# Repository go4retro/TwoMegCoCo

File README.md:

# TwoMegCoCo - an SRAM-based 2048kB RAM Expansion for the TANDY Color Computer 3
A TTL logic, SRAM-based 2048kB (2MB) memory expansion for the Color Computer 3.  Upper bank registers are write-only, like the older Disto units. All parts are through hole for easy hobbyist assembly.

## Motivation

After acquiring a used Disto 2MB memory expansion, I wondered if a similar 1980's TTL-based solution could have been created using SRAM (ignoring the fact that 2MB of SRAM was extremely expensive at the time compared to DRAM), and I wanted to see if I could design a unit using only off-the-shelf TTL circuitry. (And, since, at time of writing this, the MMU extension PCB is still being debugged, the question is yet unanswered :-)).

Obviously, as with the HalfMegCoco project, there is little economic incentive in this project, as the contemporary commercial solutions offer more functionality at a cheaper price.  But, there's always some value in building a unit oneself, or at least understanding how the MMU process works by inspecting the actual TTL logic.

## Status

Currently, the SRAM board has been confirmed to work with various MMU extension solutions (Boysontech/Cloud9), but I am still designing and debugging the MMU board (would appreciate help, if there is interest).

## License
Copyright (C) 2020  RETRO Innovations

These files are free designs; you can redistribute them and/or modify
them under the terms of the Creative Commons Attribution-ShareAlike 
4.0 International License.

You should have received a copy of the license along with this
work. If not, see <http://creativecommons.org/licenses/by-sa/4.0/>.

These files are distributed in the hope that they will be useful,
but WITHOUT ANY WARRANTY; without even the implied warranty of
MERCHANTABILITY or FITNESS FOR A PARTICULAR PURPOSE.  See the
license for more details.

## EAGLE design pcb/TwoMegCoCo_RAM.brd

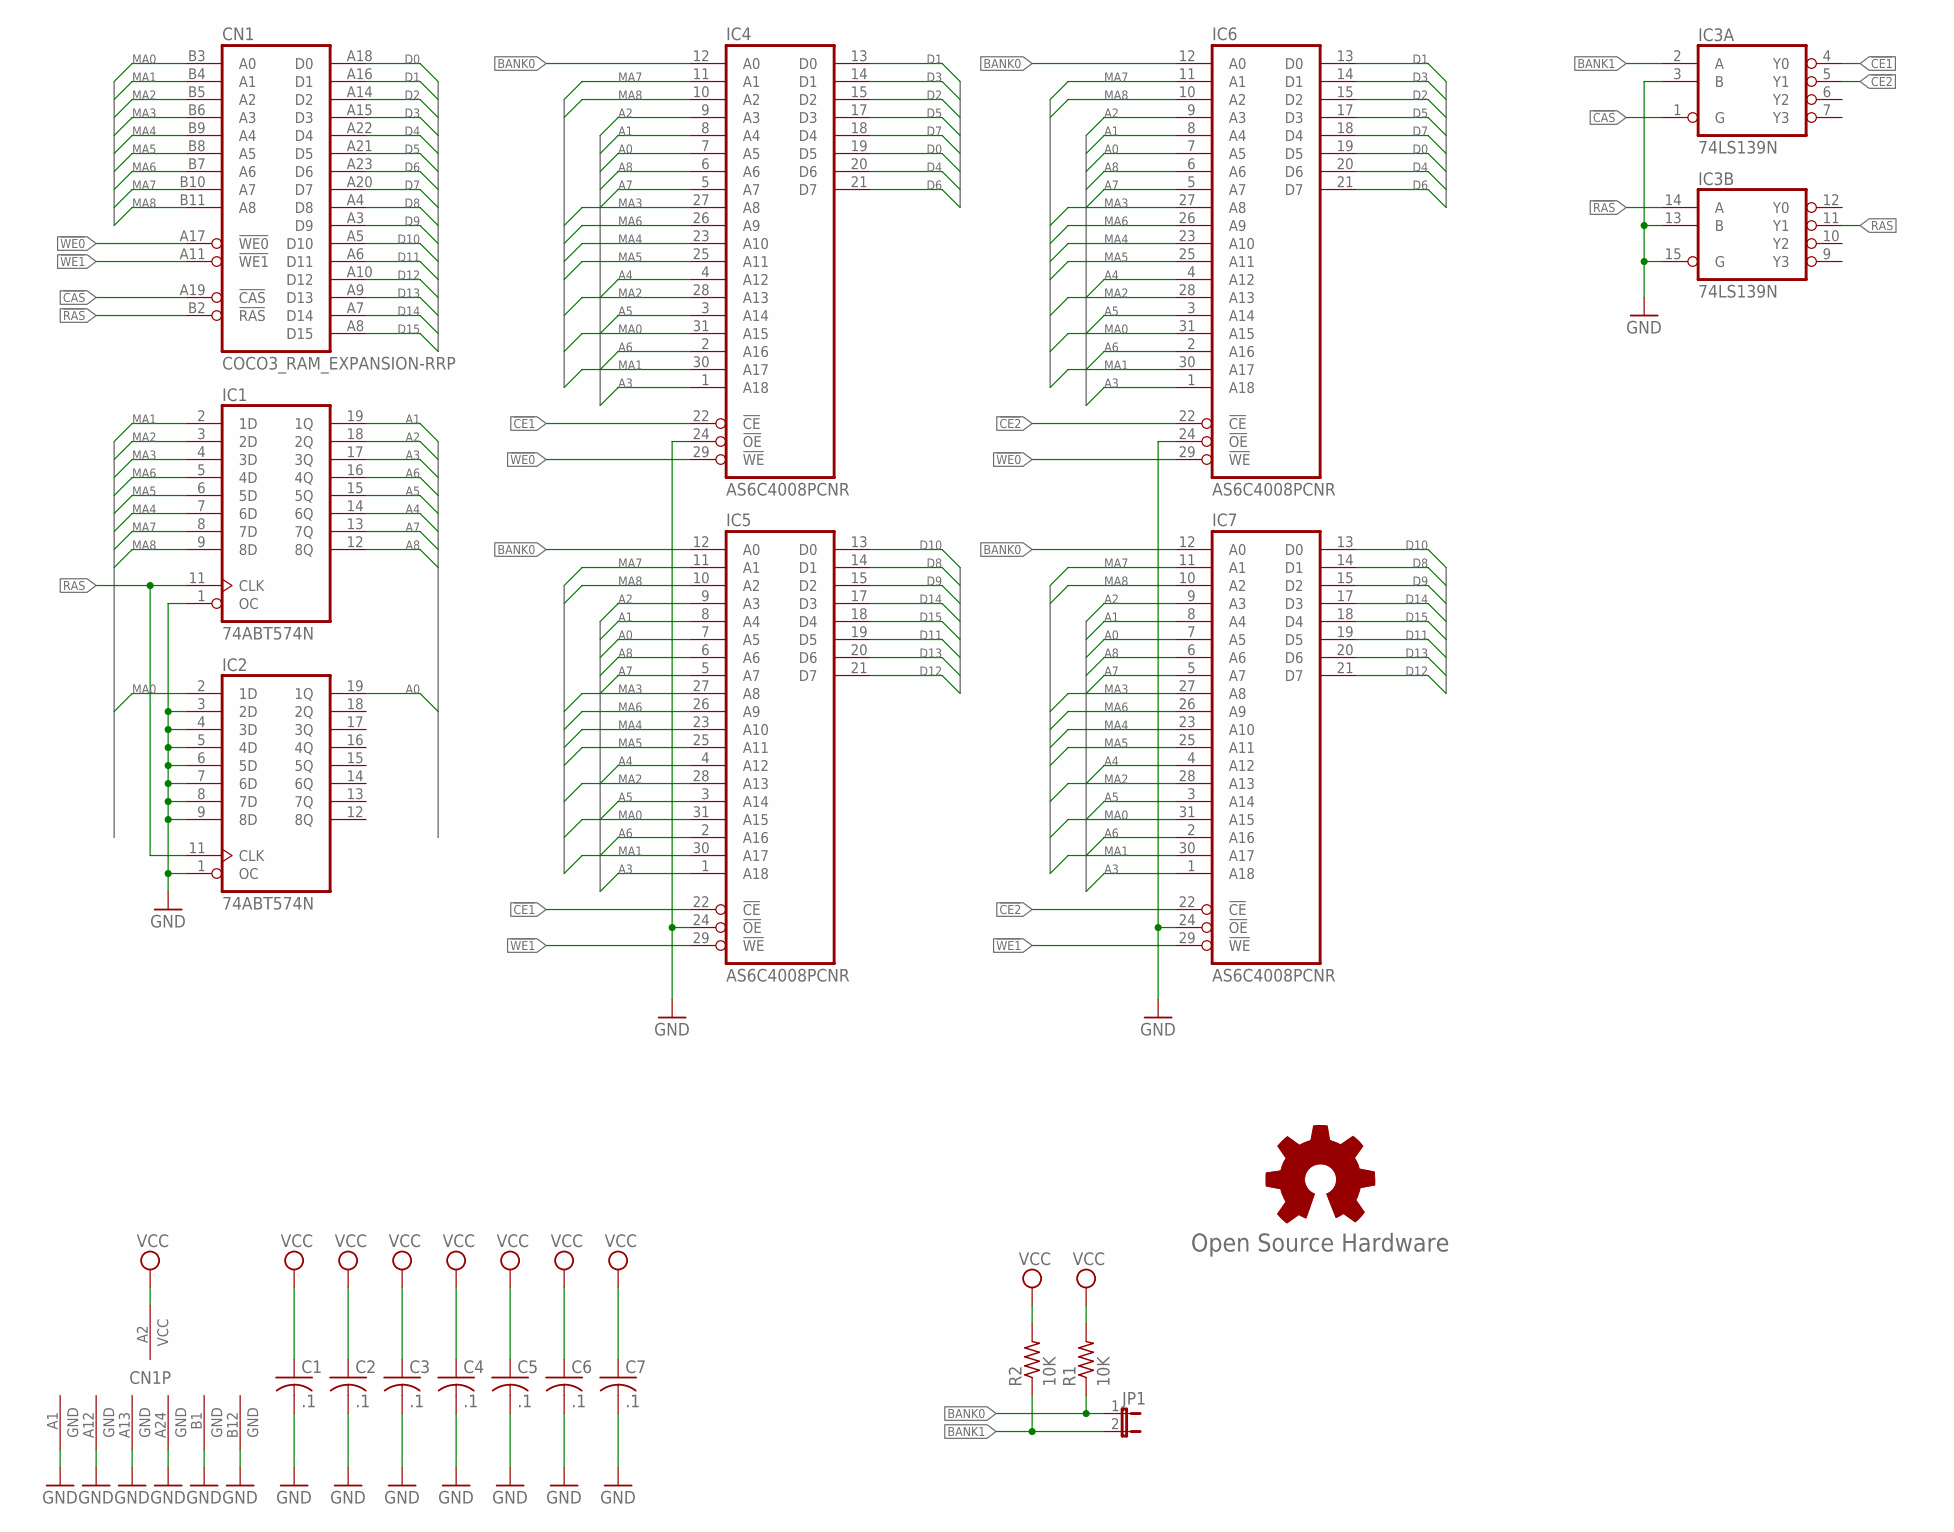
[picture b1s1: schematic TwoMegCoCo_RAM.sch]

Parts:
C1, C2, C3, C4, C5, C6, C7: .1; C025-025X050
CN1: COCO3_RAM_EXPANSION-RRP; RAM_EXPANSION_REV_RP
GOLD_ORB_SM1: Open Source Hardware; OSHW_8MM
IC1, IC2: 74ABT574N; DIL20-RP
IC3: 74LS139N; DIL16-RP
IC4, IC5, IC6, IC7: AS6C4008PCNR; DIL32-RP
JP1: JP1E; JP1
R1, R2: 10K; 0204/7

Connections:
!CAS: CN1.A19 (!CAS), IC3.1 (G)
!CE1: IC3.4 (Y0), IC4.22 (!CE), IC5.22 (!CE)
!CE2: IC3.5 (Y1), IC6.22 (!CE), IC7.22 (!CE)
!RAS: CN1.B2 (!RAS), IC3.14 (A)
!WE0: CN1.A17 (!WE0), IC4.29 (!WE), IC6.29 (!WE)
!WE1: CN1.A11 (!WE1), IC5.29 (!WE), IC7.29 (!WE)
A0: IC2.19 (1Q), IC4.7 (A5), IC5.7 (A5), IC6.7 (A5), IC7.7 (A5)
A1: IC1.19 (1Q), IC4.8 (A4), IC5.8 (A4), IC6.8 (A4), IC7.8 (A4)
A2: IC1.18 (2Q), IC4.9 (A3), IC5.9 (A3), IC6.9 (A3), IC7.9 (A3)
A3: IC1.17 (3Q), IC4.1 (A18), IC5.1 (A18), IC6.1 (A18), IC7.1 (A18)
A4: IC1.14 (6Q), IC4.4 (A12), IC5.4 (A12), IC6.4 (A12), IC7.4 (A12)
A5: IC1.15 (5Q), IC4.3 (A14), IC5.3 (A14), IC6.3 (A14), IC7.3 (A14)
A6: IC1.16 (4Q), IC4.2 (A16), IC5.2 (A16), IC6.2 (A16), IC7.2 (A16)
A7: IC1.13 (7Q), IC4.5 (A7), IC5.5 (A7), IC6.5 (A7), IC7.5 (A7)
A8: IC1.12 (8Q), IC4.6 (A6), IC5.6 (A6), IC6.6 (A6), IC7.6 (A6)
BANK0: IC4.12 (A0), IC5.12 (A0), IC6.12 (A0), IC7.12 (A0), JP1.1, R1.1
BANK1: IC3.2 (A), JP1.2, R2.1
D0: CN1.A18 (D0), IC4.19 (D5), IC6.19 (D5)
D1: CN1.A16 (D1), IC4.13 (D0), IC6.13 (D0)
D2: CN1.A14 (D2), IC4.15 (D2), IC6.15 (D2)
D3: CN1.A15 (D3), IC4.14 (D1), IC6.14 (D1)
D4: CN1.A22 (D4), IC4.20 (D6), IC6.20 (D6)
D5: CN1.A21 (D5), IC4.17 (D3), IC6.17 (D3)
D6: CN1.A23 (D6), IC4.21 (D7), IC6.21 (D7)
D7: CN1.A20 (D7), IC4.18 (D4), IC6.18 (D4)
D8: CN1.A4 (D8), IC5.14 (D1), IC7.14 (D1)
D9: CN1.A3 (D9), IC5.15 (D2), IC7.15 (D2)
D10: CN1.A5 (D10), IC5.13 (D0), IC7.13 (D0)
D11: CN1.A6 (D11), IC5.19 (D5), IC7.19 (D5)
D12: CN1.A10 (D12), IC5.21 (D7), IC7.21 (D7)
D13: CN1.A9 (D13), IC5.20 (D6), IC7.20 (D6)
D14: CN1.A7 (D14), IC5.17 (D3), IC7.17 (D3)
D15: CN1.A8 (D15), IC5.18 (D4), IC7.18 (D4)
GND: C1.2, C2.2, C3.2, C4.2, C5.2, C6.2, C7.2, CN1.A1 (GND), CN1.A12 (GND), CN1.A13 (GND), CN1.A24 (GND), CN1.B1 (GND), CN1.B12 (GND), IC1.1 (OC), IC1.10 (GND), IC2.1 (OC), IC2.3 (2D), IC2.4 (3D), IC2.5 (4D), IC2.6 (5D), IC2.7 (6D), IC2.8 (7D), IC2.9 (8D), IC2.10 (GND), IC3.3 (B), IC3.8 (GND), IC3.13 (B), IC3.15 (G), IC4.16 (GND), IC4.24 (!OE), IC5.16 (GND), IC5.24 (!OE), IC6.16 (GND), IC6.24 (!OE), IC7.16 (GND), IC7.24 (!OE)
MA0: CN1.B3 (A0), IC2.2 (1D), IC4.31 (A15), IC5.31 (A15), IC6.31 (A15), IC7.31 (A15)
MA1: CN1.B4 (A1), IC1.2 (1D), IC4.30 (A17), IC5.30 (A17), IC6.30 (A17), IC7.30 (A17)
MA2: CN1.B5 (A2), IC1.3 (2D), IC4.28 (A13), IC5.28 (A13), IC6.28 (A13), IC7.28 (A13)
MA3: CN1.B6 (A3), IC1.4 (3D), IC4.27 (A8), IC5.27 (A8), IC6.27 (A8), IC7.27 (A8)
MA4: CN1.B9 (A4), IC1.7 (6D), IC4.23 (A10), IC5.23 (A10), IC6.23 (A10), IC7.23 (A10)
MA5: CN1.B8 (A5), IC1.6 (5D), IC4.25 (A11), IC5.25 (A11), IC6.25 (A11), IC7.25 (A11)
MA6: CN1.B7 (A6), IC1.5 (4D), IC4.26 (A9), IC5.26 (A9), IC6.26 (A9), IC7.26 (A9)
MA7: CN1.B10 (A7), IC1.8 (7D), IC4.11 (A1), IC5.11 (A1), IC6.11 (A1), IC7.11 (A1)
MA8: CN1.B11 (A8), IC1.9 (8D), IC4.10 (A2), IC5.10 (A2), IC6.10 (A2), IC7.10 (A2)
RAS: IC1.11 (CLK), IC2.11 (CLK), IC3.11 (Y1)
VCC: C1.1, C2.1, C3.1, C4.1, C5.1, C6.1, C7.1, CN1.A2 (VCC), IC1.20 (VCC), IC2.20 (VCC), IC3.16 (VCC), IC4.32 (VCC), IC5.32 (VCC), IC6.32 (VCC), IC7.32 (VCC), R1.2, R2.2

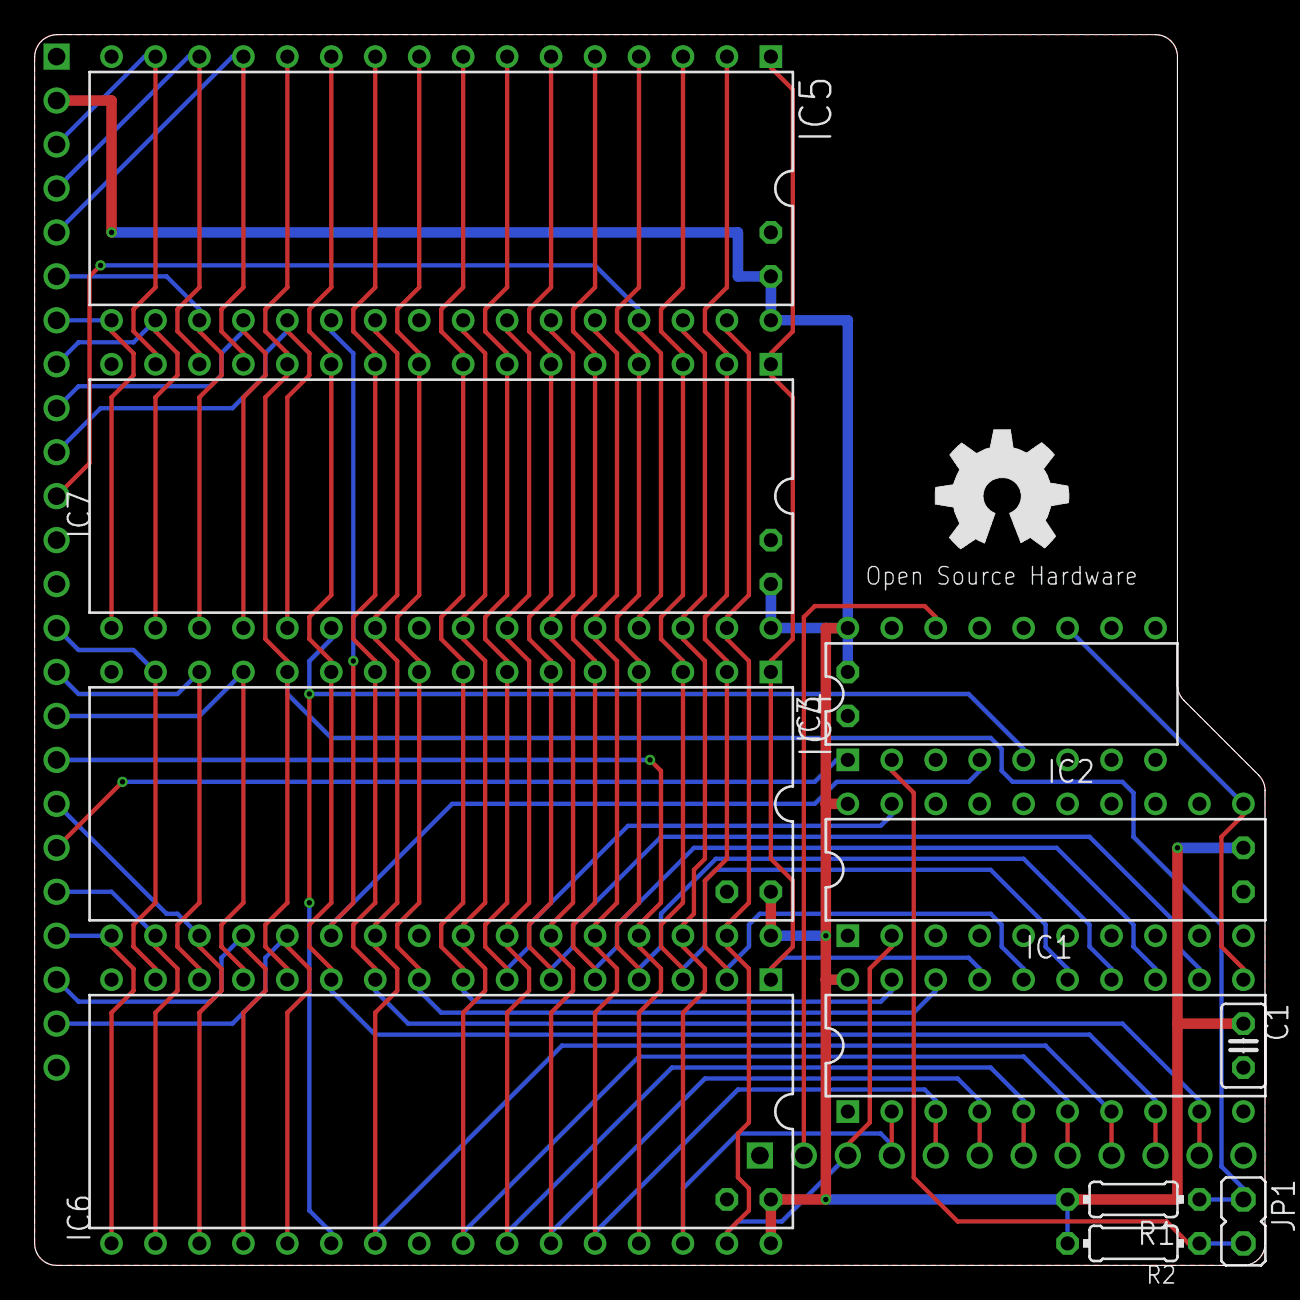
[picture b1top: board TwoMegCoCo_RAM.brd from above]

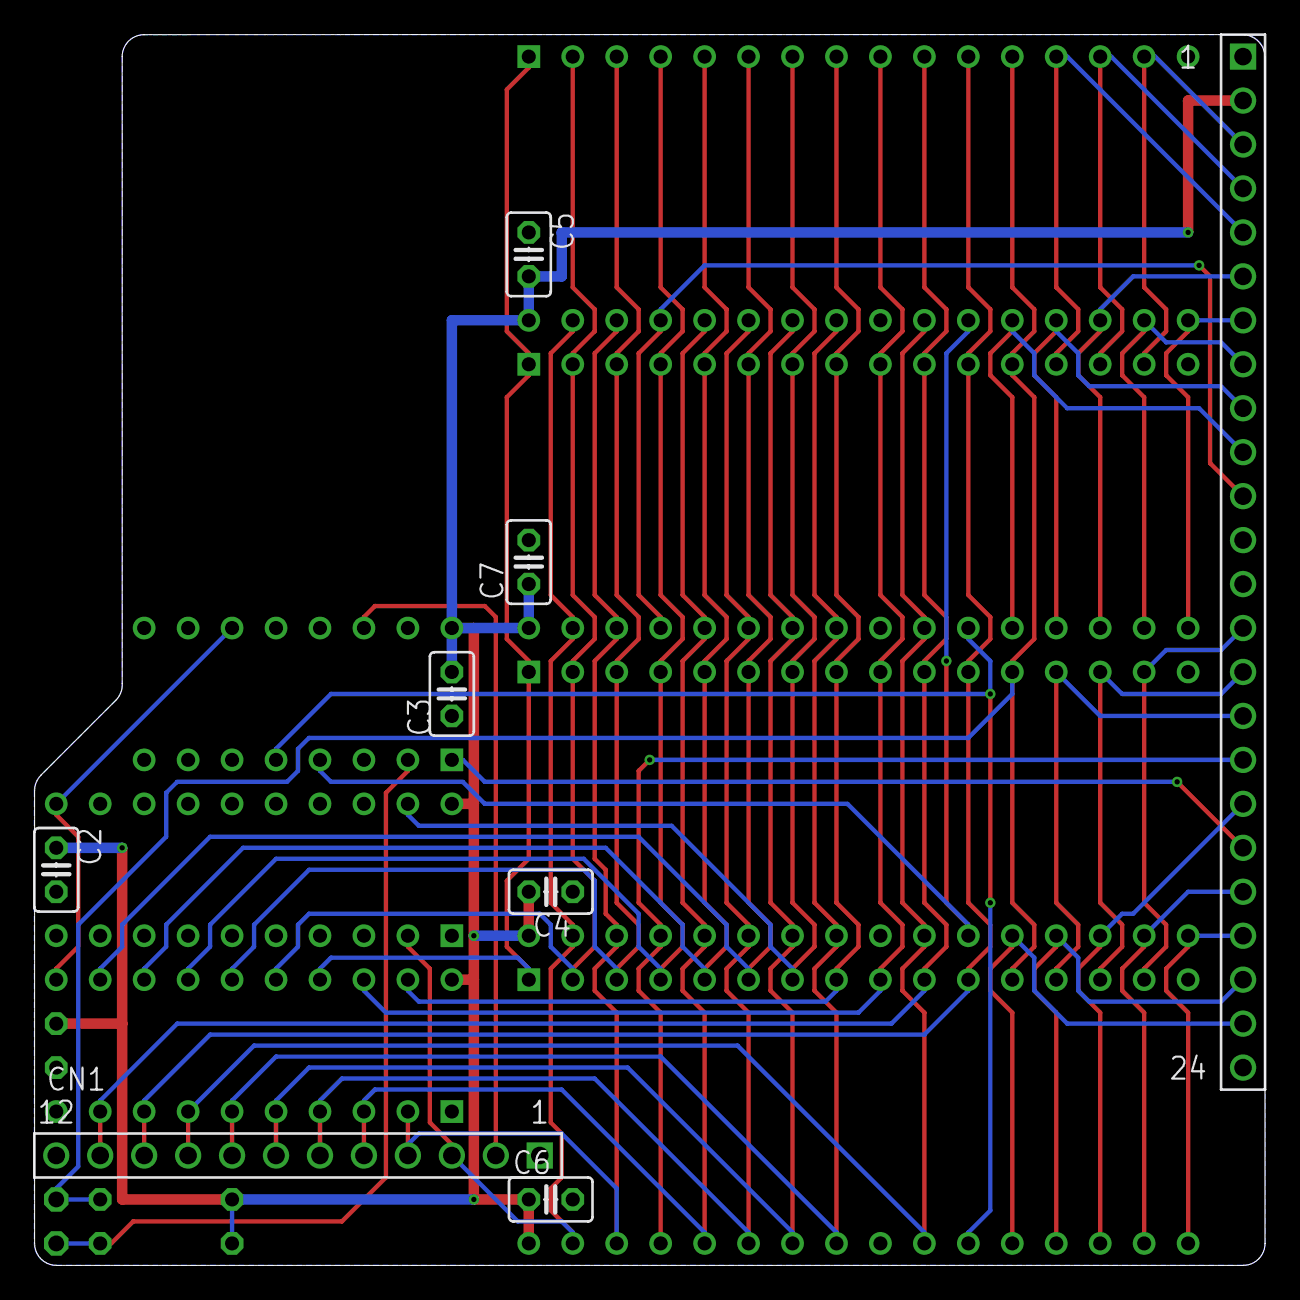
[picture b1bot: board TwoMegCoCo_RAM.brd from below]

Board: 2 copper layers, 71.1 x 71.1 mm, 19 parts (6 on the bottom side), 45 nets.

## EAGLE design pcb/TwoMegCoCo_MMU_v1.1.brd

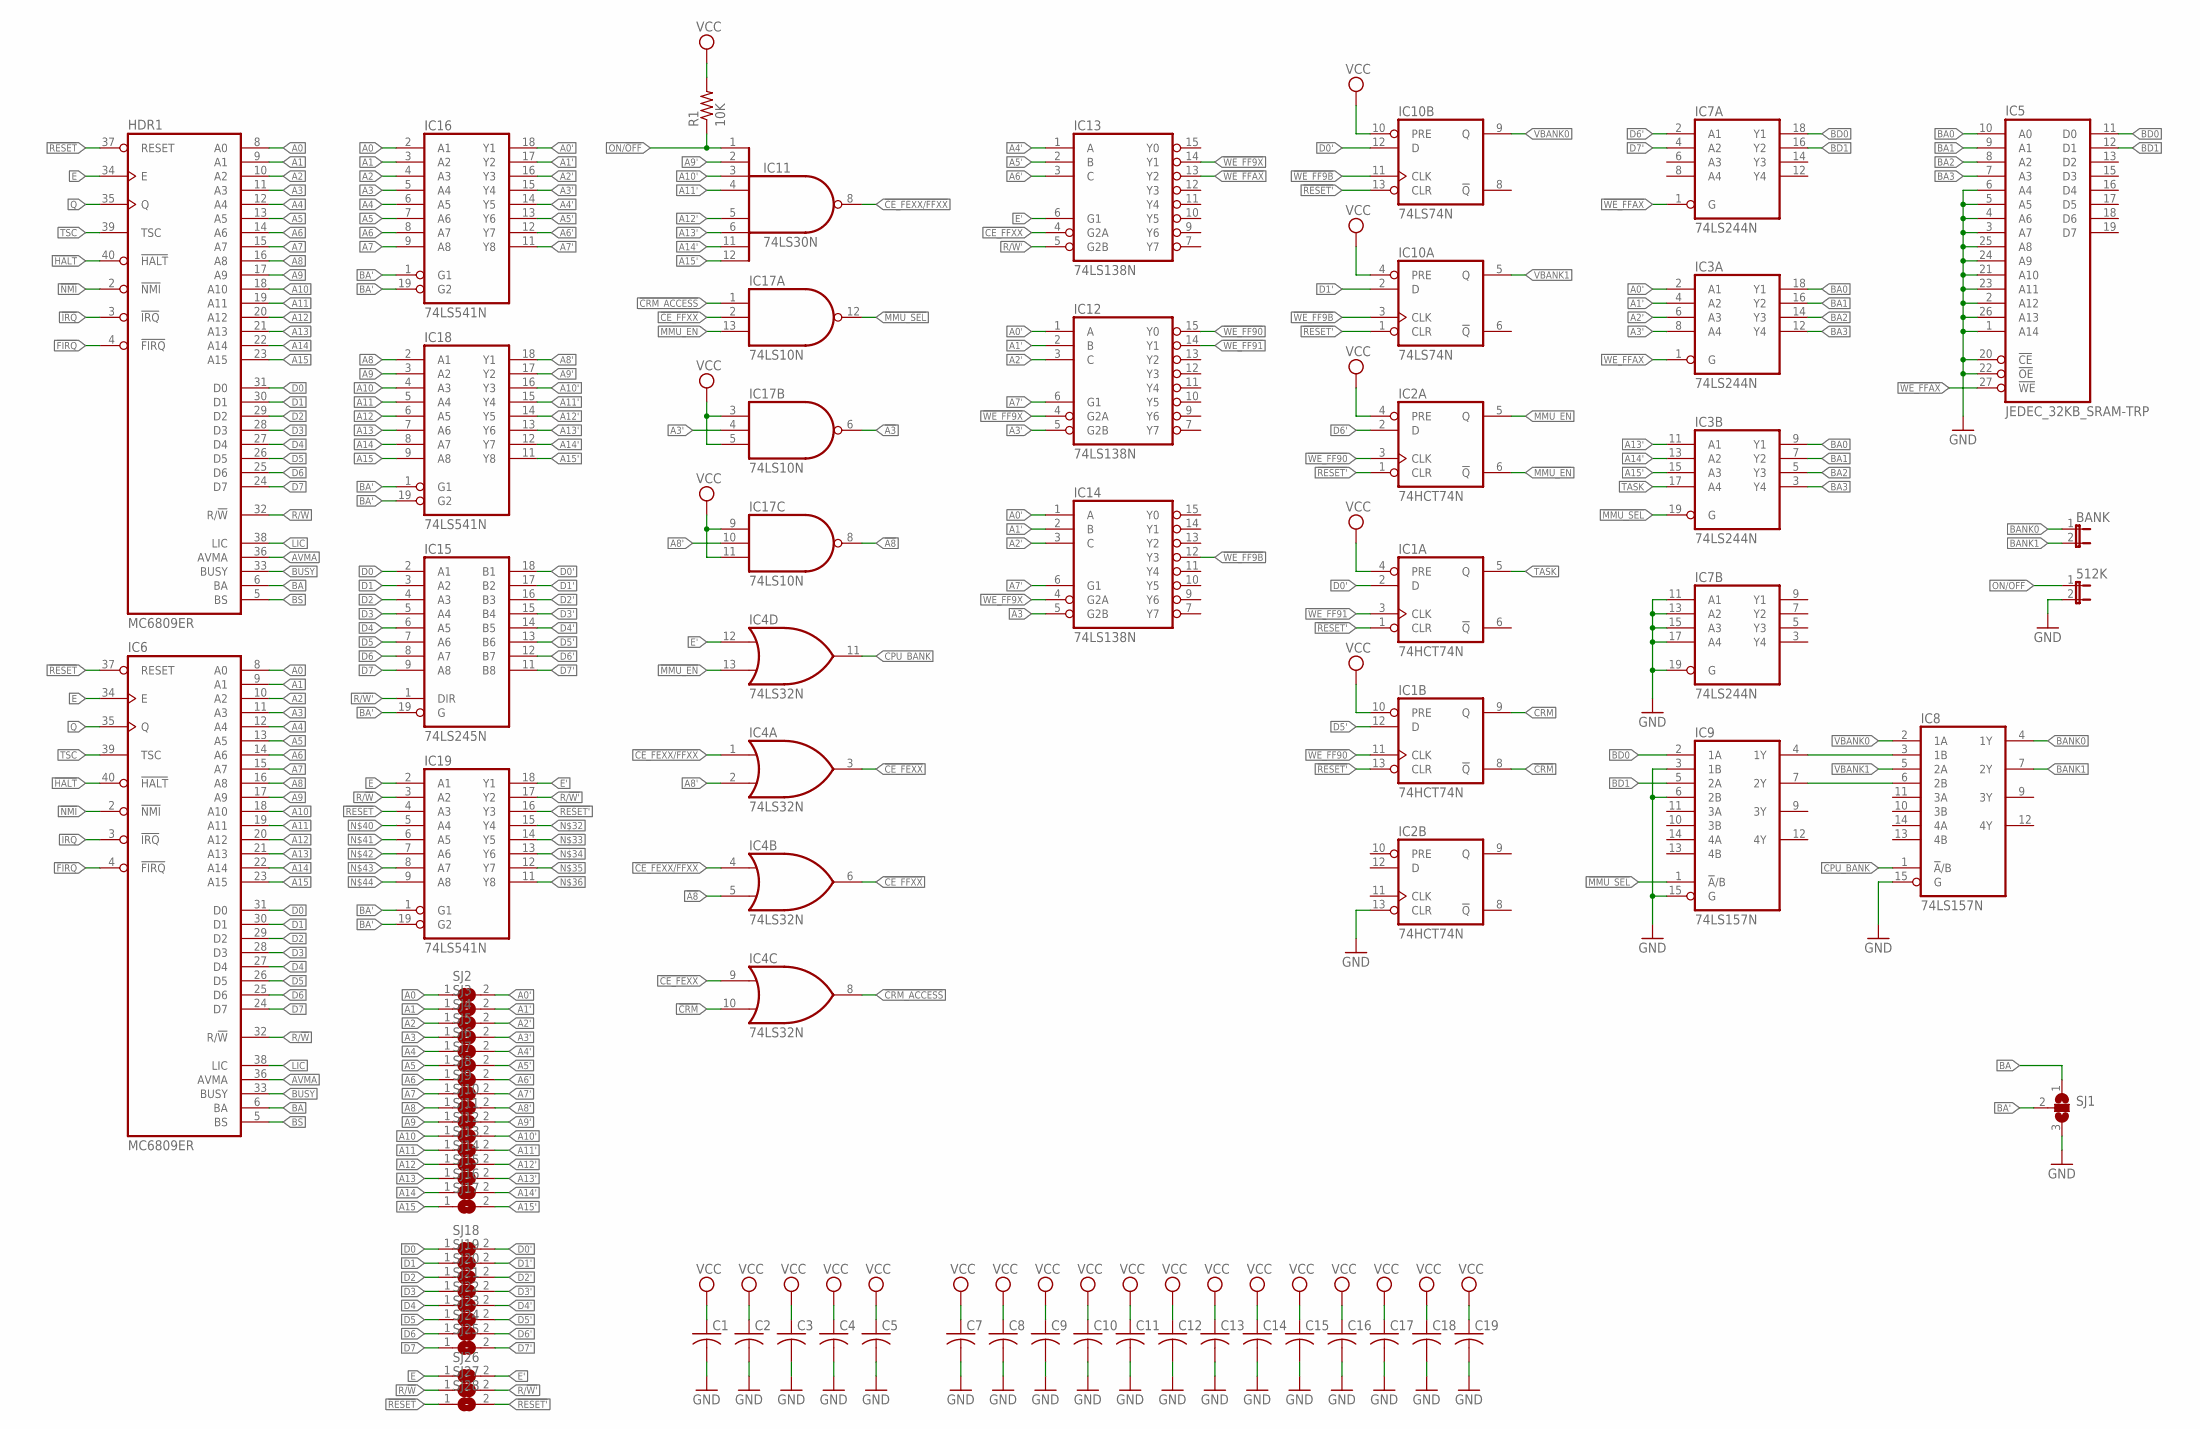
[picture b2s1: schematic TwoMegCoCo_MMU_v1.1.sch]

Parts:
512K: JP1E; JP1
BANK: JP1E; JP1
C1, C2, C3, C4, C5, C7, C8, C9, C10, C11, C12, C13, C14, C15, C16, C17, C18, C19: C-US025-025X050; C025-025X050
HDR1: MC6809ER; DIL40-ROUNDPAD
IC1, IC2: 74HCT74N; DIL14-RP
IC3, IC7: 74LS244N; DIL20-RP
IC4: 74LS32N; DIL14-RP
IC5: JEDEC_32KB_SRAM-TRP; DIL28-3-RP
IC6: MC6809ER; DIL40-ROUNDPAD
IC8, IC9: 74LS157N; DIL16-RP
IC10: 74LS74N; DIL14-RP
IC11: 74LS30N; DIL14-RP
IC12, IC13, IC14: 74LS138N; DIL16-RP
IC15: 74LS245N; DIL20-RP
IC16, IC18, IC19: 74LS541N; DIL20-RP
IC17: 74LS10N; DIL14-RP
R1: 10K; 0204/7
SJ1: SJ2W; SJ_2
SJ2, SJ3, SJ4, SJ5, SJ6, SJ7, SJ8, SJ9, SJ10, SJ11, SJ12, SJ13, SJ14, SJ15, SJ16, SJ17, SJ18, SJ19, SJ20, SJ21, SJ22, SJ23, SJ24, SJ25, SJ26, SJ27, SJ28: SJ

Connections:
!A3: IC14.5 (G2B), IC17.6 (O)
!A8: IC4.5 (I1), IC17.8 (O)
!CE_FEXX: IC4.3 (O), IC4.9 (I0)
!CE_FEXX/FFXX: IC4.1 (I0), IC4.4 (I0), IC11.8 (O)
!CE_FFXX: IC4.6 (O), IC13.4 (G2A), IC17.2 (I1)
!CRM: IC1.8 (!Q), IC4.10 (I1)
!CRM_ACCESS: IC4.8 (O), IC17.1 (I0)
!FIRQ: HDR1.4 (!FIRQ), IC6.4 (!FIRQ)
!HALT: HDR1.40 (!HALT), IC6.40 (!HALT)
!IRQ: HDR1.3 (!IRQ), IC6.3 (!IRQ)
!MMU_EN: IC2.6 (!Q), IC4.13 (I1)
!MMU_SEL: IC3.19 (G), IC9.1 (!A!/B), IC17.12 (O)
!NMI: HDR1.2 (!NMI), IC6.2 (!NMI)
!RESET: HDR1.37 (RESET), IC6.37 (RESET), IC19.4 (A3), SJ28.1
!RESET': IC1.1 (CLR), IC1.13 (CLR), IC2.1 (CLR), IC10.1 (CLR), IC10.13 (CLR), IC19.16 (Y3), SJ28.2
!WE_FF9B: IC10.3 (CLK), IC10.11 (CLK), IC14.12 (Y3)
!WE_FF9X: IC12.4 (G2A), IC13.14 (Y1), IC14.4 (G2A)
!WE_FF90: IC1.11 (CLK), IC2.3 (CLK), IC12.15 (Y0)
!WE_FF91: IC1.3 (CLK), IC12.14 (Y1)
!WE_FFAX: IC3.1 (G), IC5.27 (!WE), IC7.1 (G), IC13.13 (Y2)
A0: HDR1.8 (A0), IC6.8 (A0), IC16.2 (A1), SJ2.1
A0': IC3.2 (A1), IC12.1 (A), IC14.1 (A), IC16.18 (Y1), SJ2.2
A1: HDR1.9 (A1), IC6.9 (A1), IC16.3 (A2), SJ3.1
A1': IC3.4 (A2), IC12.2 (B), IC14.2 (B), IC16.17 (Y2), SJ3.2
A2: HDR1.10 (A2), IC6.10 (A2), IC16.4 (A3), SJ4.1
A2': IC3.6 (A3), IC12.3 (C), IC14.3 (C), IC16.16 (Y3), SJ4.2
A3: HDR1.11 (A3), IC6.11 (A3), IC16.5 (A4), SJ5.1
A3': IC3.8 (A4), IC12.5 (G2B), IC16.15 (Y4), IC17.4 (I1), SJ5.2
A4: HDR1.12 (A4), IC6.12 (A4), IC16.6 (A5), SJ6.1
A4': IC13.1 (A), IC16.14 (Y5), SJ6.2
A5: HDR1.13 (A5), IC6.13 (A5), IC16.7 (A6), SJ7.1
A5': IC13.2 (B), IC16.13 (Y6), SJ7.2
A6: HDR1.14 (A6), IC6.14 (A6), IC16.8 (A7), SJ8.1
A6': IC13.3 (C), IC16.12 (Y7), SJ8.2
A7: HDR1.15 (A7), IC6.15 (A7), IC16.9 (A8), SJ9.1
A7': IC12.6 (G1), IC14.6 (G1), IC16.11 (Y8), SJ9.2
A8: HDR1.16 (A8), IC6.16 (A8), IC18.2 (A1), SJ10.1
A8': IC4.2 (I1), IC17.10 (I1), IC18.18 (Y1), SJ10.2
A9: HDR1.17 (A9), IC6.17 (A9), IC18.3 (A2), SJ11.1
A9': IC11.2 (I1), IC18.17 (Y2), SJ11.2
A10: HDR1.18 (A10), IC6.18 (A10), IC18.4 (A3), SJ12.1
A10': IC11.3 (I2), IC18.16 (Y3), SJ12.2
A11: HDR1.19 (A11), IC6.19 (A11), IC18.5 (A4), SJ13.1
A11': IC11.4 (I3), IC18.15 (Y4), SJ13.2
A12: HDR1.20 (A12), IC6.20 (A12), IC18.6 (A5), SJ14.1
A12': IC11.5 (I4), IC18.14 (Y5), SJ14.2
A13: HDR1.21 (A13), IC6.21 (A13), IC18.7 (A6), SJ15.1
A13': IC3.11 (A1), IC11.6 (I5), IC18.13 (Y6), SJ15.2
A14: HDR1.22 (A14), IC6.22 (A14), IC18.8 (A7), SJ16.1
A14': IC3.13 (A2), IC11.11 (I6), IC18.12 (Y7), SJ16.2
A15: HDR1.23 (A15), IC6.23 (A15), IC18.9 (A8), SJ17.1
A15': IC3.15 (A3), IC11.12 (I7), IC18.11 (Y8), SJ17.2
AVMA: HDR1.36 (AVMA), IC6.36 (AVMA)
BA: HDR1.6 (BA), IC6.6 (BA), SJ1.1
BA0: IC3.9 (Y1), IC3.18 (Y1), IC5.10 (A0)
BA1: IC3.7 (Y2), IC3.16 (Y2), IC5.9 (A1)
BA2: IC3.5 (Y3), IC3.14 (Y3), IC5.8 (A2)
BA3: IC3.3 (Y4), IC3.12 (Y4), IC5.7 (A3)
BA': IC15.19 (G), IC16.1 (G1), IC16.19 (G2), IC18.1 (G1), IC18.19 (G2), IC19.1 (G1), IC19.19 (G2), SJ1.2
BANK0: BANK.1, IC8.4 (1Y)
BANK1: BANK.2, IC8.7 (2Y)
BD0: IC5.11 (D0), IC7.18 (Y1), IC9.2 (1A)
BD1: IC5.12 (D1), IC7.16 (Y2), IC9.5 (2A)
BS: HDR1.5 (BS), IC6.5 (BS)
BUSY: HDR1.33 (BUSY), IC6.33 (BUSY)
CPU_BANK: IC4.11 (O), IC8.1 (!A!/B)
CRM: IC1.9 (Q)
D0: HDR1.31 (D0), IC6.31 (D0), IC15.2 (A1), SJ18.1
D0': IC1.2 (D), IC10.12 (D), IC15.18 (B1), SJ18.2
D1: HDR1.30 (D1), IC6.30 (D1), IC15.3 (A2), SJ19.1
D1': IC10.2 (D), IC15.17 (B2), SJ19.2
D2: HDR1.29 (D2), IC6.29 (D2), IC15.4 (A3), SJ20.1
D2': IC15.16 (B3), SJ20.2
D3: HDR1.28 (D3), IC6.28 (D3), IC15.5 (A4), SJ21.1
D3': IC15.15 (B4), SJ21.2
D4: HDR1.27 (D4), IC6.27 (D4), IC15.6 (A5), SJ22.1
D4': IC15.14 (B5), SJ22.2
D5: HDR1.26 (D5), IC6.26 (D5), IC15.7 (A6), SJ23.1
D5': IC1.12 (D), IC15.13 (B6), SJ23.2
D6: HDR1.25 (D6), IC6.25 (D6), IC15.8 (A7), SJ24.1
D6': IC2.2 (D), IC7.2 (A1), IC15.12 (B7), SJ24.2
D7: HDR1.24 (D7), IC6.24 (D7), IC15.9 (A8), SJ25.1
D7': IC7.4 (A2), IC15.11 (B8), SJ25.2
E: HDR1.34 (E), IC6.34 (E), IC19.2 (A1), SJ26.1
E': IC4.12 (I0), IC13.6 (G1), IC19.18 (Y1), SJ26.2
GND: 512K.2, C1.2, C2.2, C3.2, C4.2, C5.2, C7.2, C8.2, C9.2, C10.2, C11.2, C12.2, C13.2, C14.2, C15.2, C16.2, C17.2, C18.2, C19.2, IC1.7 (GND), IC2.7 (GND), IC2.13 (CLR), IC3.10 (GND), IC4.7 (GND), IC5.1 (A14), IC5.2 (A12), IC5.3 (A7), IC5.4 (A6), IC5.5 (A5), IC5.6 (A4), IC5.14 (GND), IC5.20 (!CE), IC5.21 (A10), IC5.22 (!OE), IC5.23 (A11), IC5.24 (A9), IC5.25 (A8), IC5.26 (A13), IC7.10 (GND), IC7.11 (A1), IC7.13 (A2), IC7.15 (A3), IC7.17 (A4), IC7.19 (G), IC8.8 (GND), IC8.15 (G), IC9.3 (1B), IC9.6 (2B), IC9.8 (GND), IC9.15 (G), IC10.7 (GND), IC11.7 (GND), IC12.8 (GND), IC13.8 (GND), IC14.8 (GND), IC15.10 (GND), IC16.10 (GND), IC17.7 (GND), IC18.10 (GND), IC19.10 (GND), SJ1.3
LIC: HDR1.38 (LIC), IC6.38 (LIC)
MMU_EN: IC2.5 (Q), IC17.13 (I2)
unnamed: IC8.3 (1B), IC9.4 (1Y)
unnamed: IC8.6 (2B), IC9.7 (2Y)
ON/!OFF: 512K.1, IC11.1 (I0), R1.1
Q: HDR1.35 (Q), IC6.35 (Q)
R/!W: HDR1.32 (R/!W), IC6.32 (R/!W), IC19.3 (A2), SJ27.1
R/!W': IC13.5 (G2B), IC15.1 (DIR), IC19.17 (Y2), SJ27.2
TASK: IC1.5 (Q), IC3.17 (A4)
TSC: HDR1.39 (TSC), IC6.39 (TSC)
VBANK0: IC8.2 (1A), IC10.9 (Q)
VBANK1: IC8.5 (2A), IC10.5 (Q)
VCC: C1.1, C2.1, C3.1, C4.1, C5.1, C7.1, C8.1, C9.1, C10.1, C11.1, C12.1, C13.1, C14.1, C15.1, C16.1, C17.1, C18.1, C19.1, HDR1.7 (VCC), IC1.4 (PRE), IC1.10 (PRE), IC1.14 (VCC), IC2.4 (PRE), IC2.14 (VCC), IC3.20 (VCC), IC4.14 (VCC), IC5.28 (VCC), IC6.7 (VCC), IC7.20 (VCC), IC8.16 (VCC), IC9.16 (VCC), IC10.4 (PRE), IC10.10 (PRE), IC10.14 (VCC), IC11.14 (VCC), IC12.16 (VCC), IC13.16 (VCC), IC14.16 (VCC), IC15.20 (VCC), IC16.20 (VCC), IC17.3 (I0), IC17.5 (I2), IC17.9 (I0), IC17.11 (I2), IC17.14 (VCC), IC18.20 (VCC), IC19.20 (VCC), R1.2
VSS: HDR1.1 (VSS), IC6.1 (VSS)

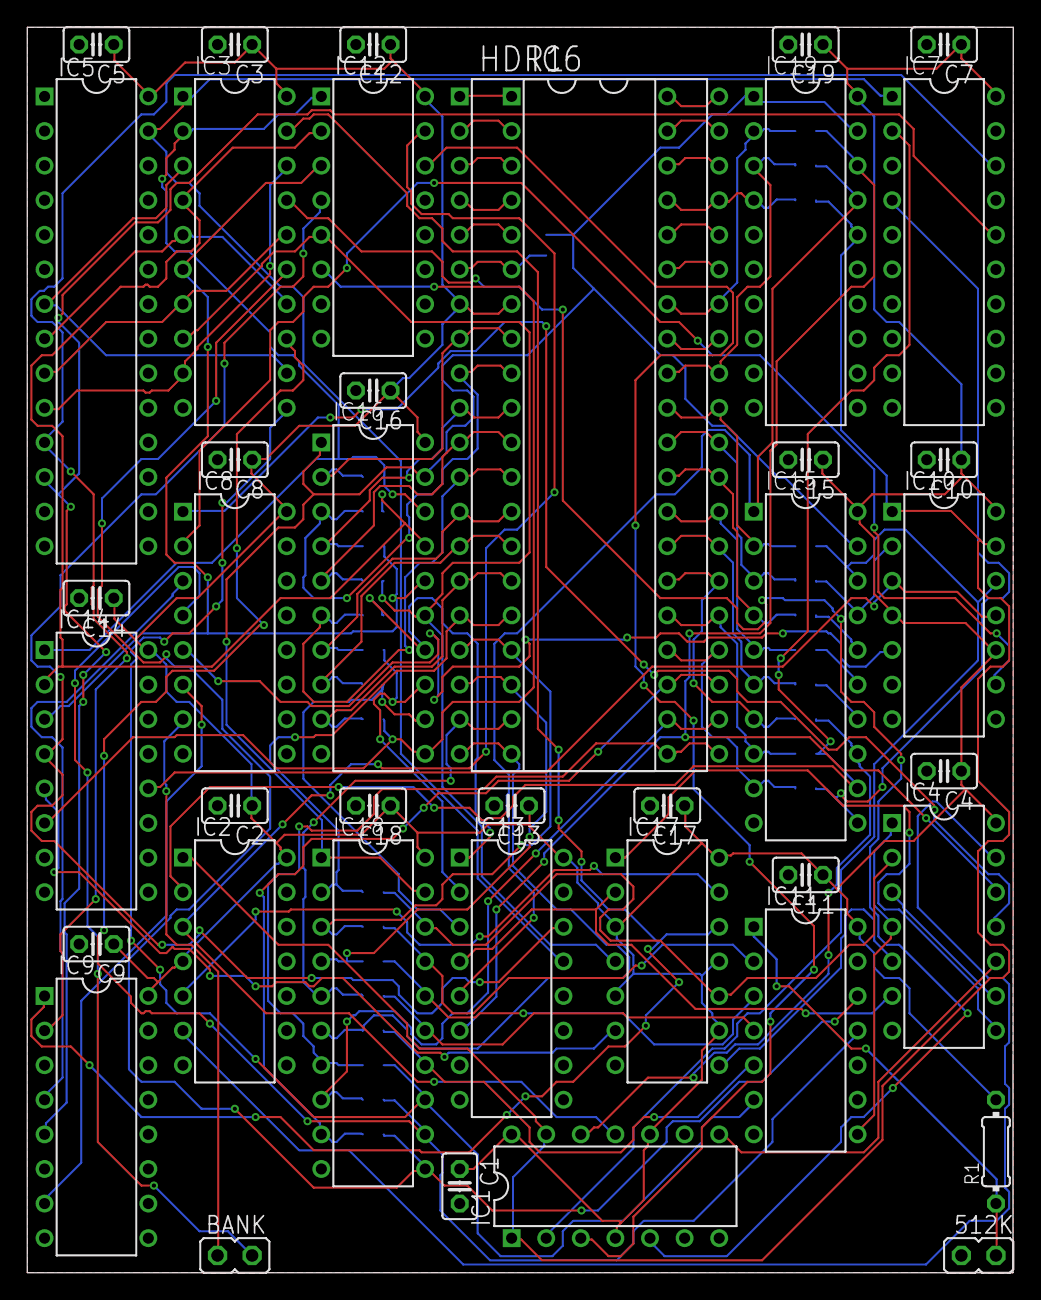
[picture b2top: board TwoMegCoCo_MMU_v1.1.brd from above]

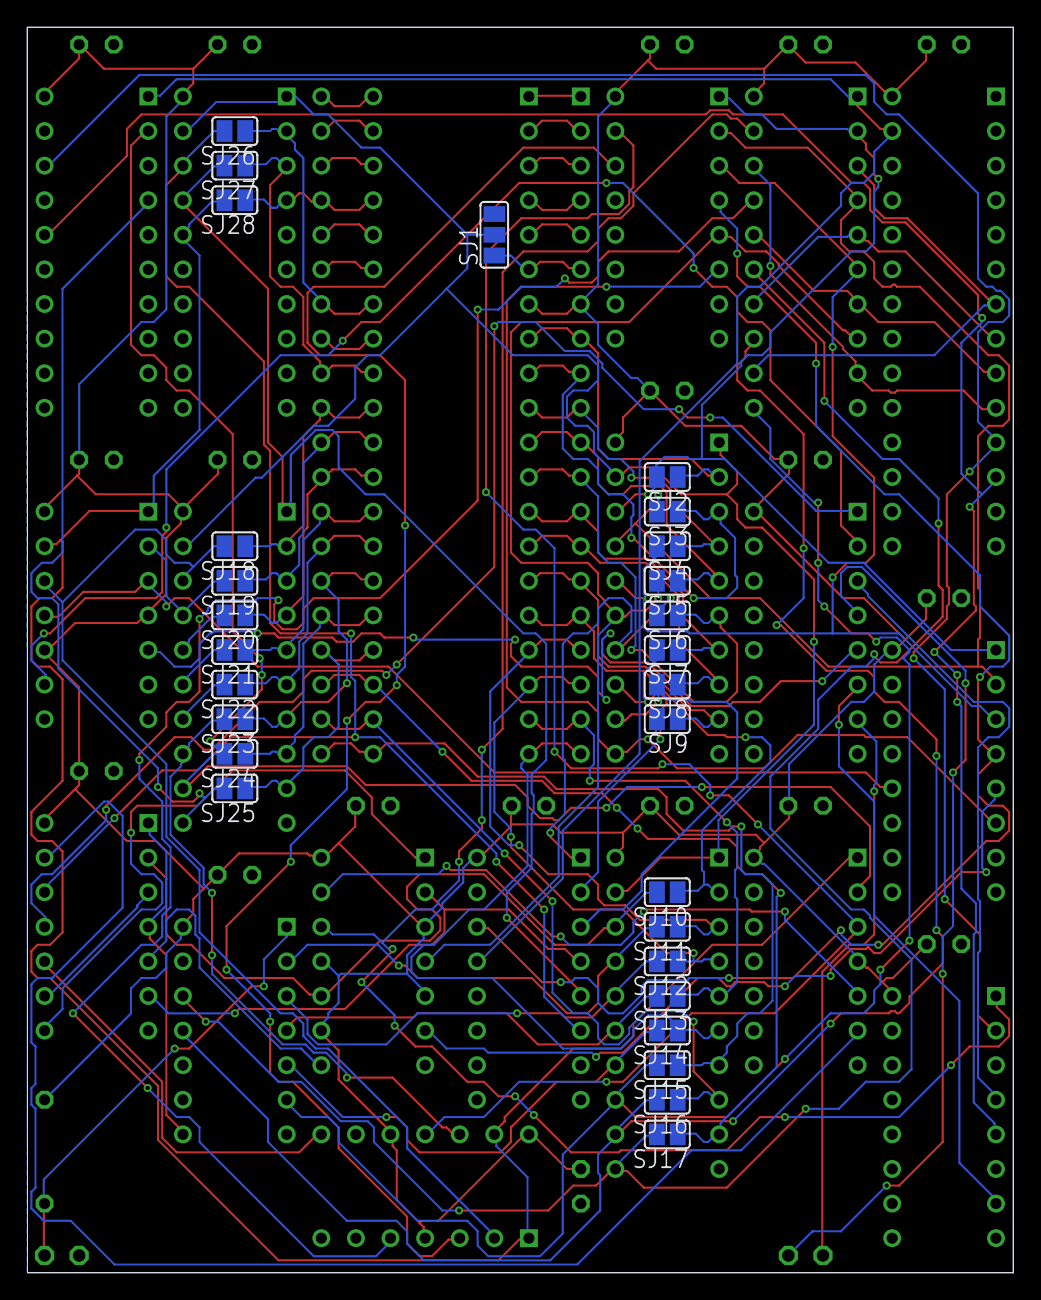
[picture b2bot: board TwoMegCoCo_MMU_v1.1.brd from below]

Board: 2 copper layers, 72.4 x 91.4 mm, 69 parts (28 on the bottom side), 99 nets.
